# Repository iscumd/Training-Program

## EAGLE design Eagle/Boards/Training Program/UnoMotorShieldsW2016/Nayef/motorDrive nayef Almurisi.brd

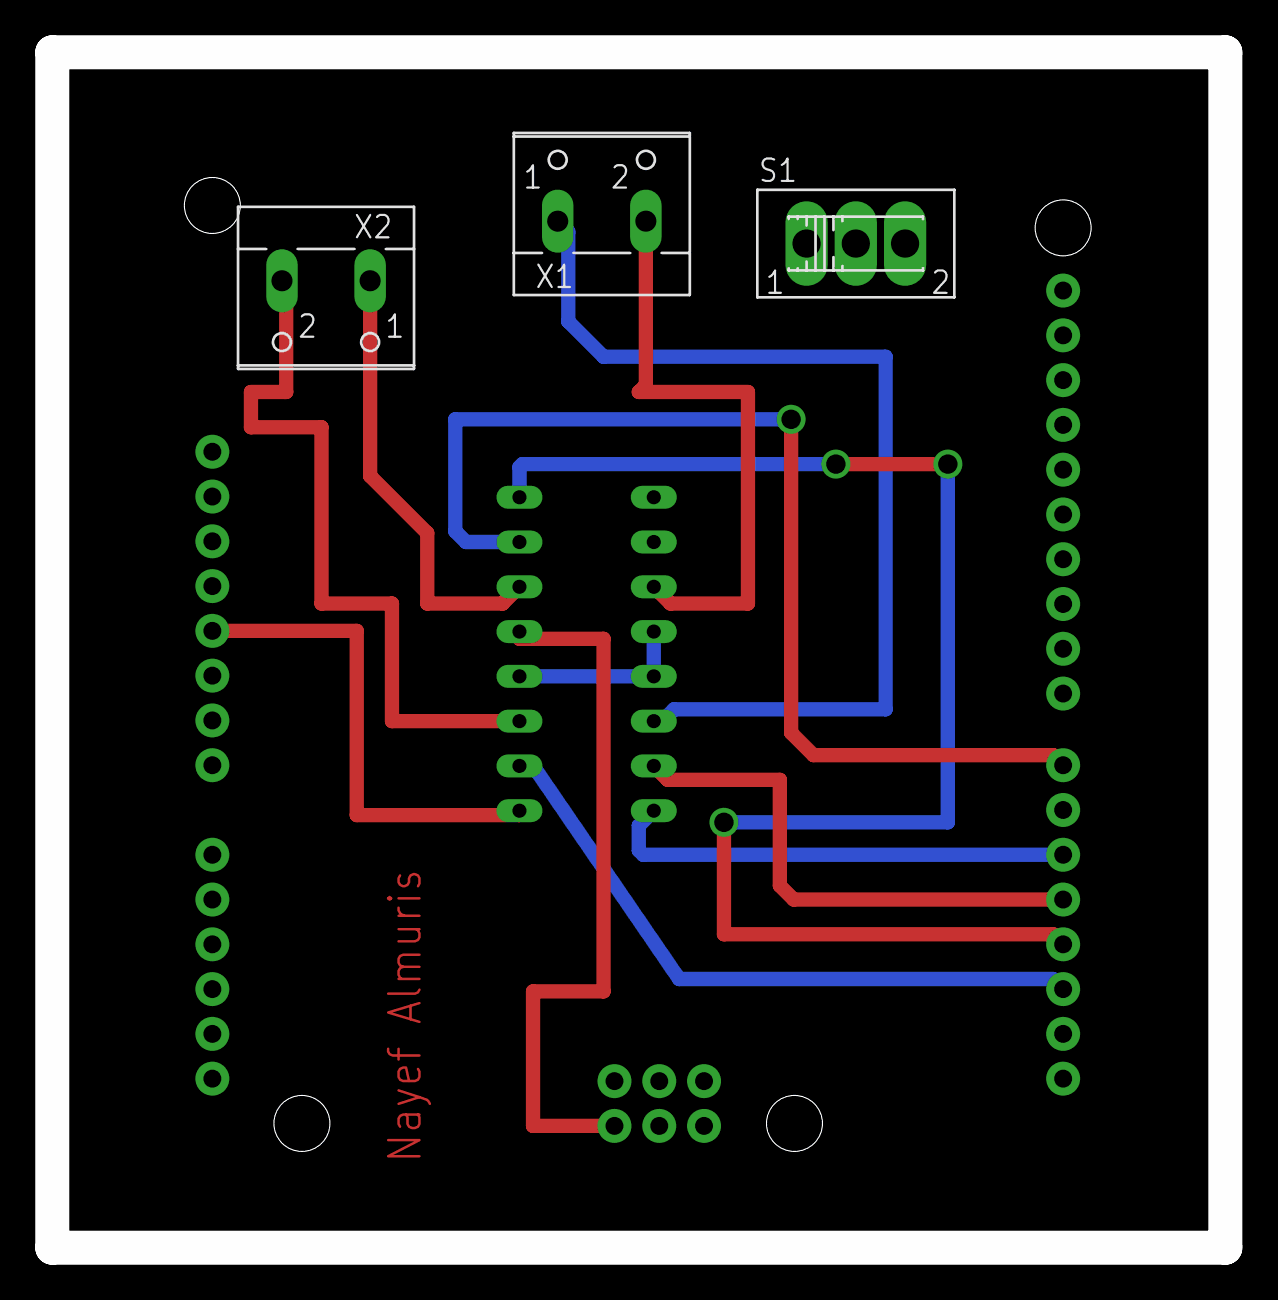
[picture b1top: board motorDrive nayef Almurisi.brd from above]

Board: 2 copper layers, 66.5 x 67.8 mm, 5 parts (0 on the bottom side), 12 nets.

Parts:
J1: ARDUINO_UNO_R3; ARDUINO_R3
S1: SLIDE_SWITCH
U$1: MOTOR_DRIVERDIP16; DIP16
X1, X2: 2PIN-SCREW-TERMINAL

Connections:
GND: U$1.P4, U$1.P5, U$1.P13
unnamed: J1.GND@4, U$1.P12
unnamed: U$1.P6, X1.2
unnamed: U$1.P3, X1.1
unnamed: U$1.P11, X2.1
unnamed: U$1.P14, X2.2
unnamed: J1.5V, U$1.P16
unnamed: J1.D3, U$1.P9
unnamed: J1.D7, U$1.P10
unnamed: J1.D4, U$1.P2
unnamed: J1.D2, U$1.P15
unnamed: J1.D5, U$1.P1

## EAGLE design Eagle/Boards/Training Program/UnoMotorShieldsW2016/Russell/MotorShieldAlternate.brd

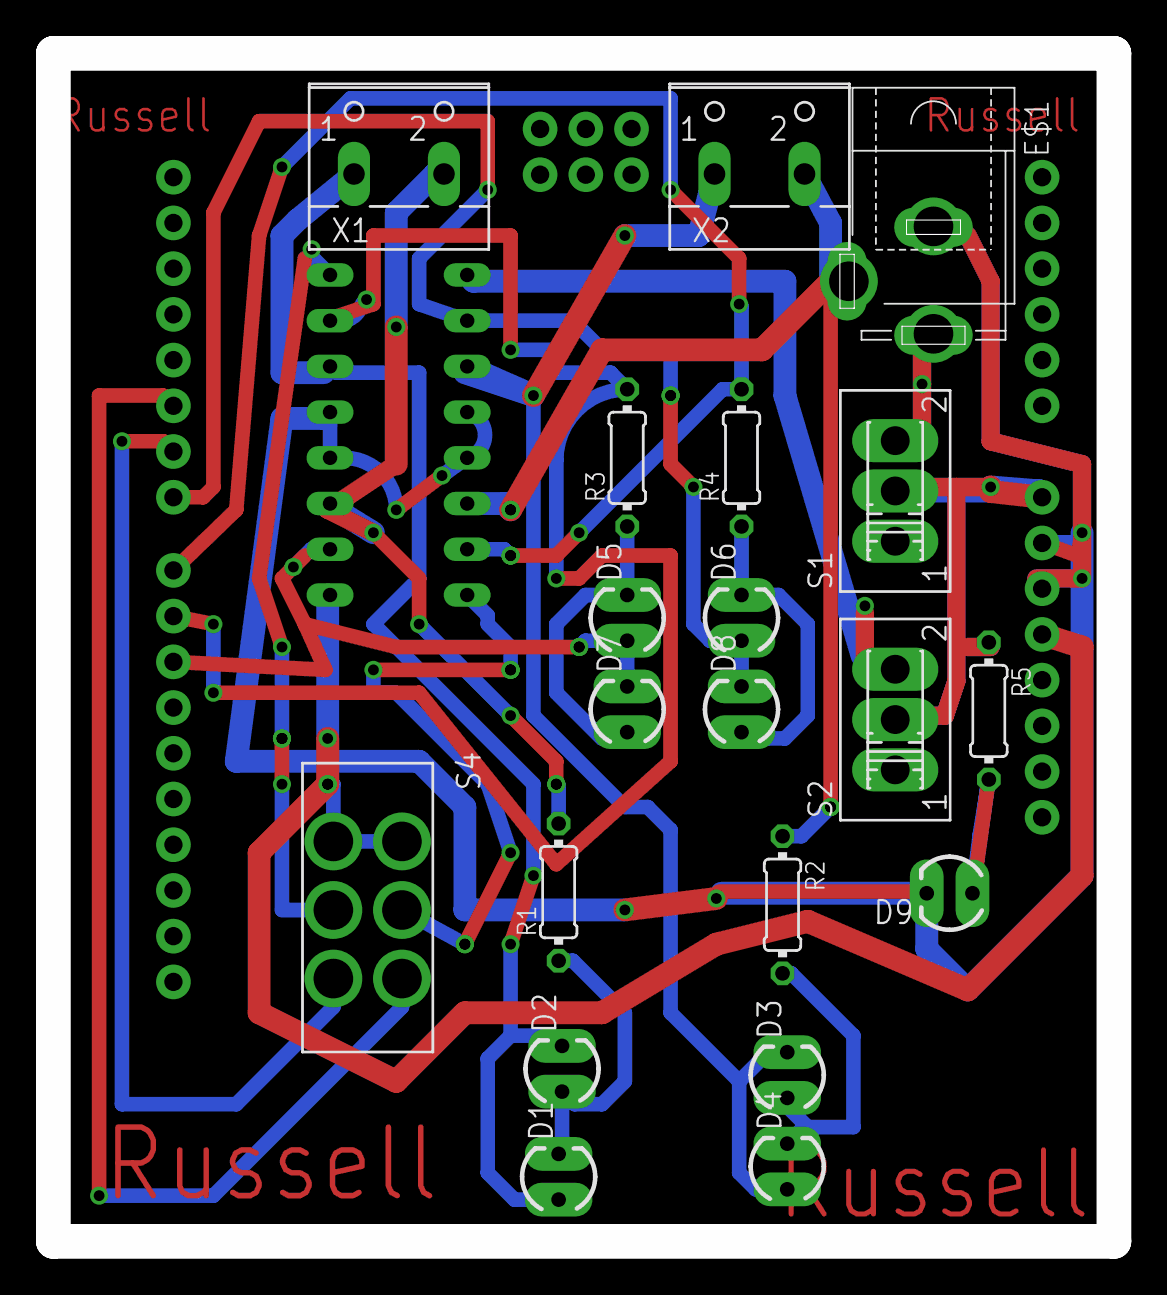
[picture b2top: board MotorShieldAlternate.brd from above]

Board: 2 copper layers, 58.9 x 66.0 mm, 22 parts (0 on the bottom side), 19 nets.

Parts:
D1, D2, D3, D4, D5, D6, D7, D8, D9: LED3MM
E$1: 5.5-2.5-BARRELCONNECTOR
J1: ARDUINO_UNO_R3; ARDUINO_R3
R1, R2, R3, R4, R5: 0204/7
S1, S2: SLIDE_SWITCH
S4: DUAL_SLIDE_SWITCH
U$1: MOTOR_DRIVERDIP16; DIP16
X1, X2: 2PIN-SCREW-TERMINAL

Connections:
unnamed: R2.1, U$1.P3
unnamed: R1.2, U$1.P14, X1.2
unnamed: J1.VIN, S1.2
unnamed: D6.A, D8.K, J1.D7, U$1.P7
unnamed: D5.A, D7.K, J1.D10
unnamed: D3.K, D4.A, U$1.P6, X2.1
unnamed: J1.D8, R4.2, U$1.P2
unnamed: J1.D9, R3.2
unnamed: D9.A, R5.2
unnamed: J1.D5, S4.6
unnamed: S4.5, U$1.P1
unnamed: J1.D6, S4.3
unnamed: D3.A, D4.K, R2.2
unnamed: D5.K, D7.A, R3.1
unnamed: D1.A, D2.K, U$1.P11, X1.1
unnamed: D1.K, D2.A, R1.1
unnamed: J1.5V, S4.1, S4.4, U$1.P16
unnamed: D9.K, J1.GND@2, U$1.P4, U$1.P5, U$1.P12, U$1.P13
unnamed: D6.K, D8.A, R4.1
